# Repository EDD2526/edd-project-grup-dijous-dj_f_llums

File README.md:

View this project on [CADLAB.io](https://cadlab.io/project/30200). 

# Projecte LLUMS

>**Autors:** 
>Martina Camprubí i Clara Rosaura

----------

## Objectiu

>PCB per control·lar les llums d'un vehicle a través d'un microcontrolador i comunicació CAN. 

## Diagrama de blocs

>

### Descripció/funcionalitat de cada bloc

  * ZONA D'ALIMENTACIÓ:
	*V-BAT 12V: Entrada de tensió provinent de la bateria del vehicle.
	*DC-DC LM2596: Converteix els 12V a 5V.
	*LDO LM1117: Redueix els 5V a 3.3V per alimentar la lògica digital.
  * CONTROL PRINCIPAL:
	*MICROCONTROLADOR: Processa entrades i controla sortides del Sistema.
	*BOTONERA: Permet a l'usuari seleccionar les diferents funcions de llum i motor.
	*USART / DEBUG: Interfície per comunicació i depuració del Sistema.
  * ZONA DIGITAL:
	*SENSOR DE LLUM (BH1750): Mesura la llum ambiental via I2C per automatizar funcions.
	*TRANSCEIVER CAN (MCP2551): Adapta els senyals del micro al bus CAN del vehicle.
	*BUS CAN: Xarxa de comuniació amb altres sistemes del vehicle.
  * ZONA DE POTÈNCIA:
	*DRIVERS MOSFET (IRLZ44N): Actuen com interruptors per controlar càrregues de 12V.
	*SISTEMA DE LLUMS: Conjunt de llums del vehicle controlades electrònicament.
	*MOTOR NETEJA-FARS: Actuador de 12V per al sistema de neteja de fars.

-----------

## Requisits / Especificacions

  * Alimentació; 12V, regulada 5V
  * Microcontrolador PIC18xxxxxxxxx
  * ...

-----------

## Components

| Descripci&#243; | Ref | Package |Datasheet | Prove&#239;dor | Preu | Unitats |
| --- | --- | --- | --- | ---| --- | --- |
| Microcontrolador | PIC18F26Q83-I/SS | SOIC-28 |[Datasheet](https://www.mouser.es/datasheet/2/268/PIC18F27_47_57Q83_Preliminary_Data_Sheet_40002265B-2887591.pdf) | [Mouser](https://www.mouser.es/c/?q=PIC18F27Q83-I%2FSO)| 2,17&euro;| 1x |
| XTAL-Ressonador | CSTCR7M99G53-R0 | SMD |[Datasheet](https://www.mouser.es/datasheet/2/281/p16e-522700.pdf) | [Mouser](https://www.mouser.es/ProductDetail/Murata-Electronics/CSTCR7M99G53-R0?qs=Zd9RUO93%2Fo7cnwzsujIkpA%3D%3D)  | 0,27&euro; | 1x |

-----------

## Software

### Eines:

  * KiCad 9.0 o superior
  * 

### Configuraci&#243; :

  * 

### Funcionalitats:

  * 

-----------

## Historial de canvis

| Data | Autor     | Branch | Versi&#243; | Descripci&#243; |
| --- | --- | --- | --- | --- |
|  28/03/2023 | mlopez | Master | initial commit | Primera versi&#243; d'esquem&#224;tic i selecci&#243; de components |

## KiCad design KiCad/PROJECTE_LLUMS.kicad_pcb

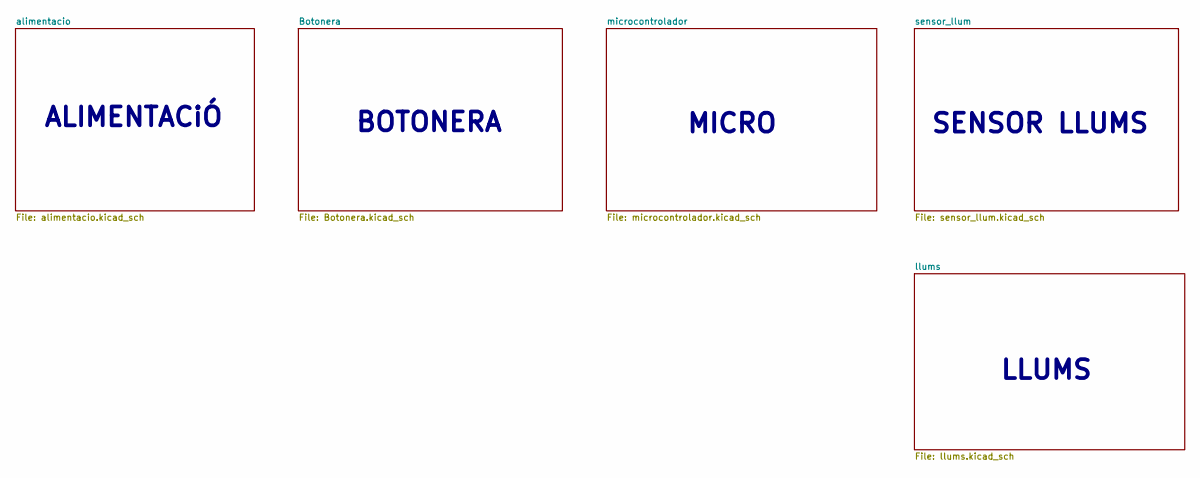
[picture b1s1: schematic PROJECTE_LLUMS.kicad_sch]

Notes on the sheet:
ALIMENTACiÓ
MICRO
LLUMS
BOTONERA
SENSOR LLUMS

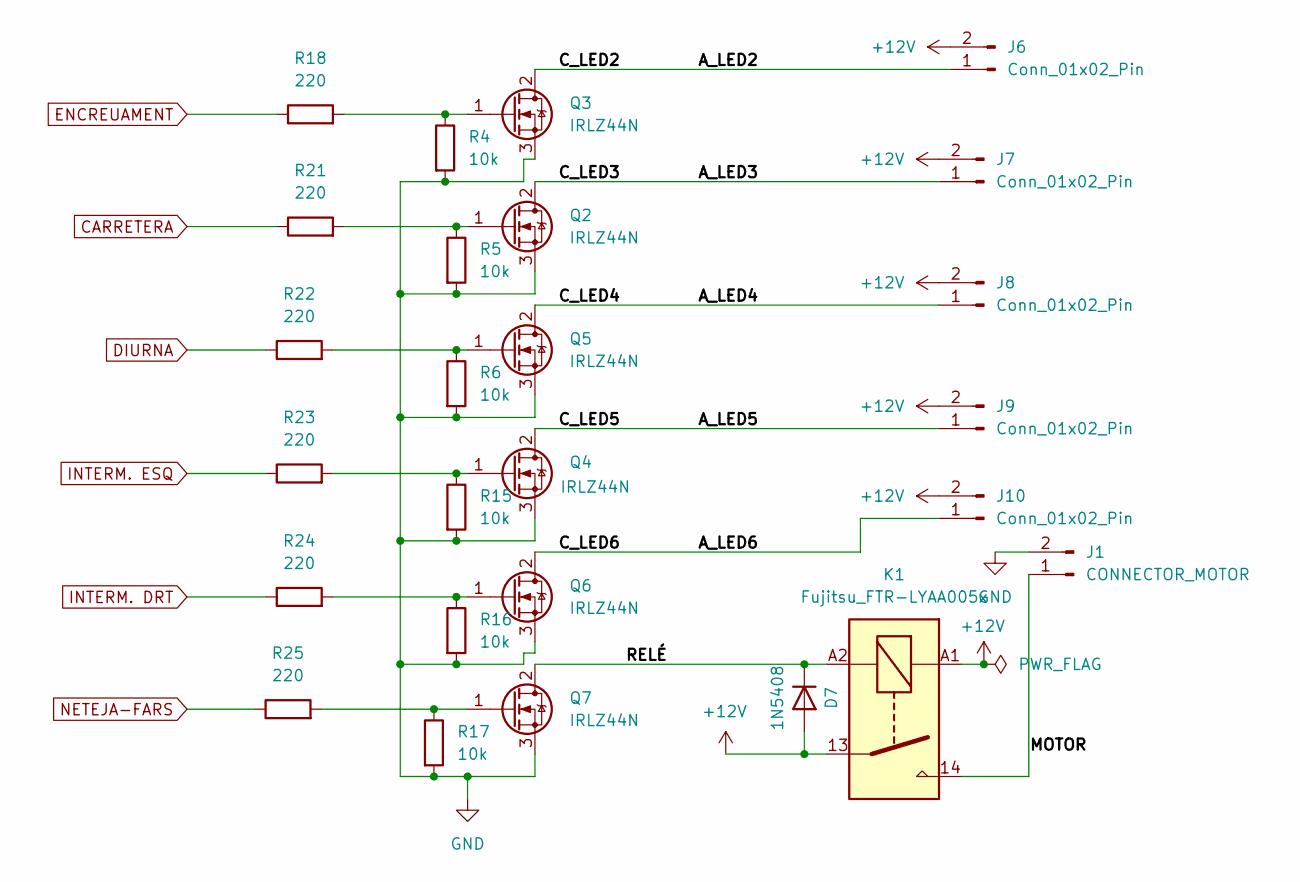
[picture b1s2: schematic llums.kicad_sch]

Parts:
D7: 1N5408; D_DO-201AD_P15.24mm_Horizontal
J1: CONNECTOR_MOTOR; JST_VH_B2P-VH_1x02_P3.96mm_Vertical
J6: Conn_01x02_Pin; TerminalBlock_Phoenix_MKDS-1,5-2-5.08_1x02_P5.08mm_Horizont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
J7, J8, J9, J10: Conn_01x02_Pin; TerminalBlock_MaiXu_MX126-5.0-02P_1x02_P5.00mm
K1: Fujitsu_FTR-LYAA005x; Relay_1-Form-C_Schrack-RYII_RM3.2mm
Q2, Q3, Q4, Q5, Q6, Q7: IRLZ44N; TO-220-3_Vertical
R4, R5, R6, R15, R16, R17: 10k; R_0805_2012Metric_Pad1.20x1.40mm_HandSolder
R18, R21, R22, R23, R24, R25: 220; R_0805_2012Metric_Pad1.20x1.40mm_HandSolder

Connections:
+12V: D7.2 (A), J6.2, J7.2, J8.2, J9.2, J10.2, K1.13, K1.A1
/llums/A_LED2: J6.1, Q3.2 (D)
/llums/A_LED3: J7.1, Q2.2 (D)
/llums/A_LED4: J8.1, Q5.2 (D)
/llums/A_LED5: J9.1, Q4.2 (D)
/llums/A_LED6: J10.1, Q6.2 (D)
/llums/MOTOR: J1.1, K1.14
/llums/RELÉ: D7.1 (K), K1.A2, Q7.2 (D)
CARRETERA: R21.1; also elsewhere on the board
DIURNA: R22.1; also elsewhere on the board
ENCREUAMENT: R18.1; also elsewhere on the board
GND: J1.2, Q2.3 (S), Q3.3 (S), Q4.3 (S), Q5.3 (S), Q6.3 (S), Q7.3 (S), R4.2, R5.2, R6.2, R15.2, R16.2, R17.2; also elsewhere on the board
INTERM. DRT: R24.1; also elsewhere on the board
INTERM. ESQ: R23.1; also elsewhere on the board
NETEJA-FARS: R25.1; also elsewhere on the board
unnamed: Q2.1 (G), R5.1, R21.2
unnamed: Q3.1 (G), R4.1, R18.2
unnamed: Q4.1 (G), R15.1, R23.2
unnamed: Q5.1 (G), R6.1, R22.2
unnamed: Q6.1 (G), R16.1, R24.2
unnamed: Q7.1 (G), R17.1, R25.2

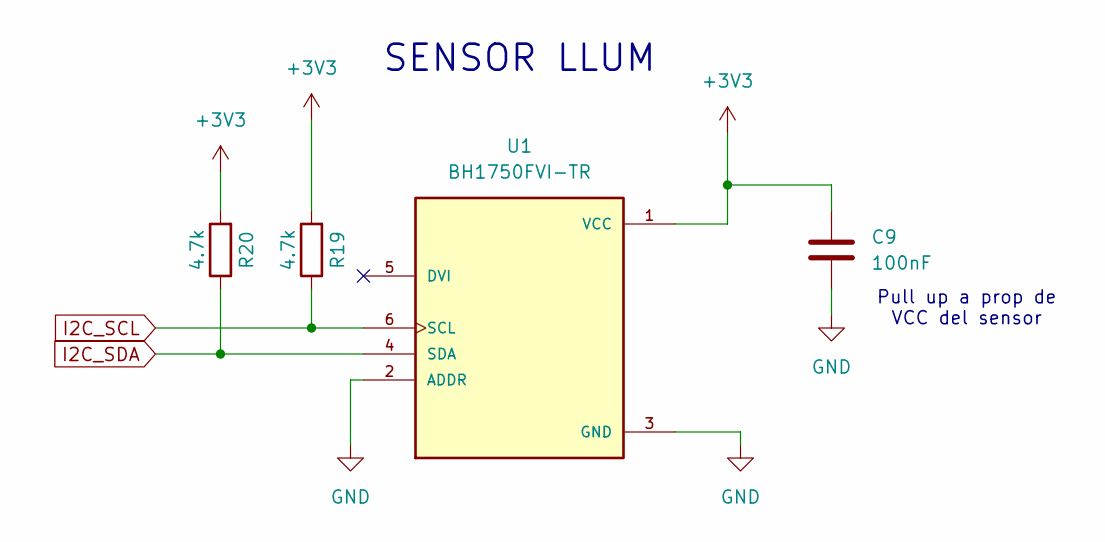
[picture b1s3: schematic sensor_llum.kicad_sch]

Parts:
C9: 100nF; C_0805_2012Metric_Pad1.18x1.45mm_HandSolder
R19, R20: 4.7k; R_0805_2012Metric_Pad1.20x1.40mm_HandSolder
U1: BH1750FVI-TR; XDCR_BH1750FVI-TR; PARTREV D

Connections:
+3V3: C9.1, R19.2, R20.2, U1.1 (VCC); also elsewhere on the board
GND: C9.2, U1.2 (ADDR), U1.3 (GND); also elsewhere on the board
I2C_SCL: R19.1, U1.6 (SCL); also elsewhere on the board
I2C_SDA: R20.1, U1.4 (SDA); also elsewhere on the board

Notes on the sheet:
SENSOR LLUM
Pull up a prop de VCC del sensor

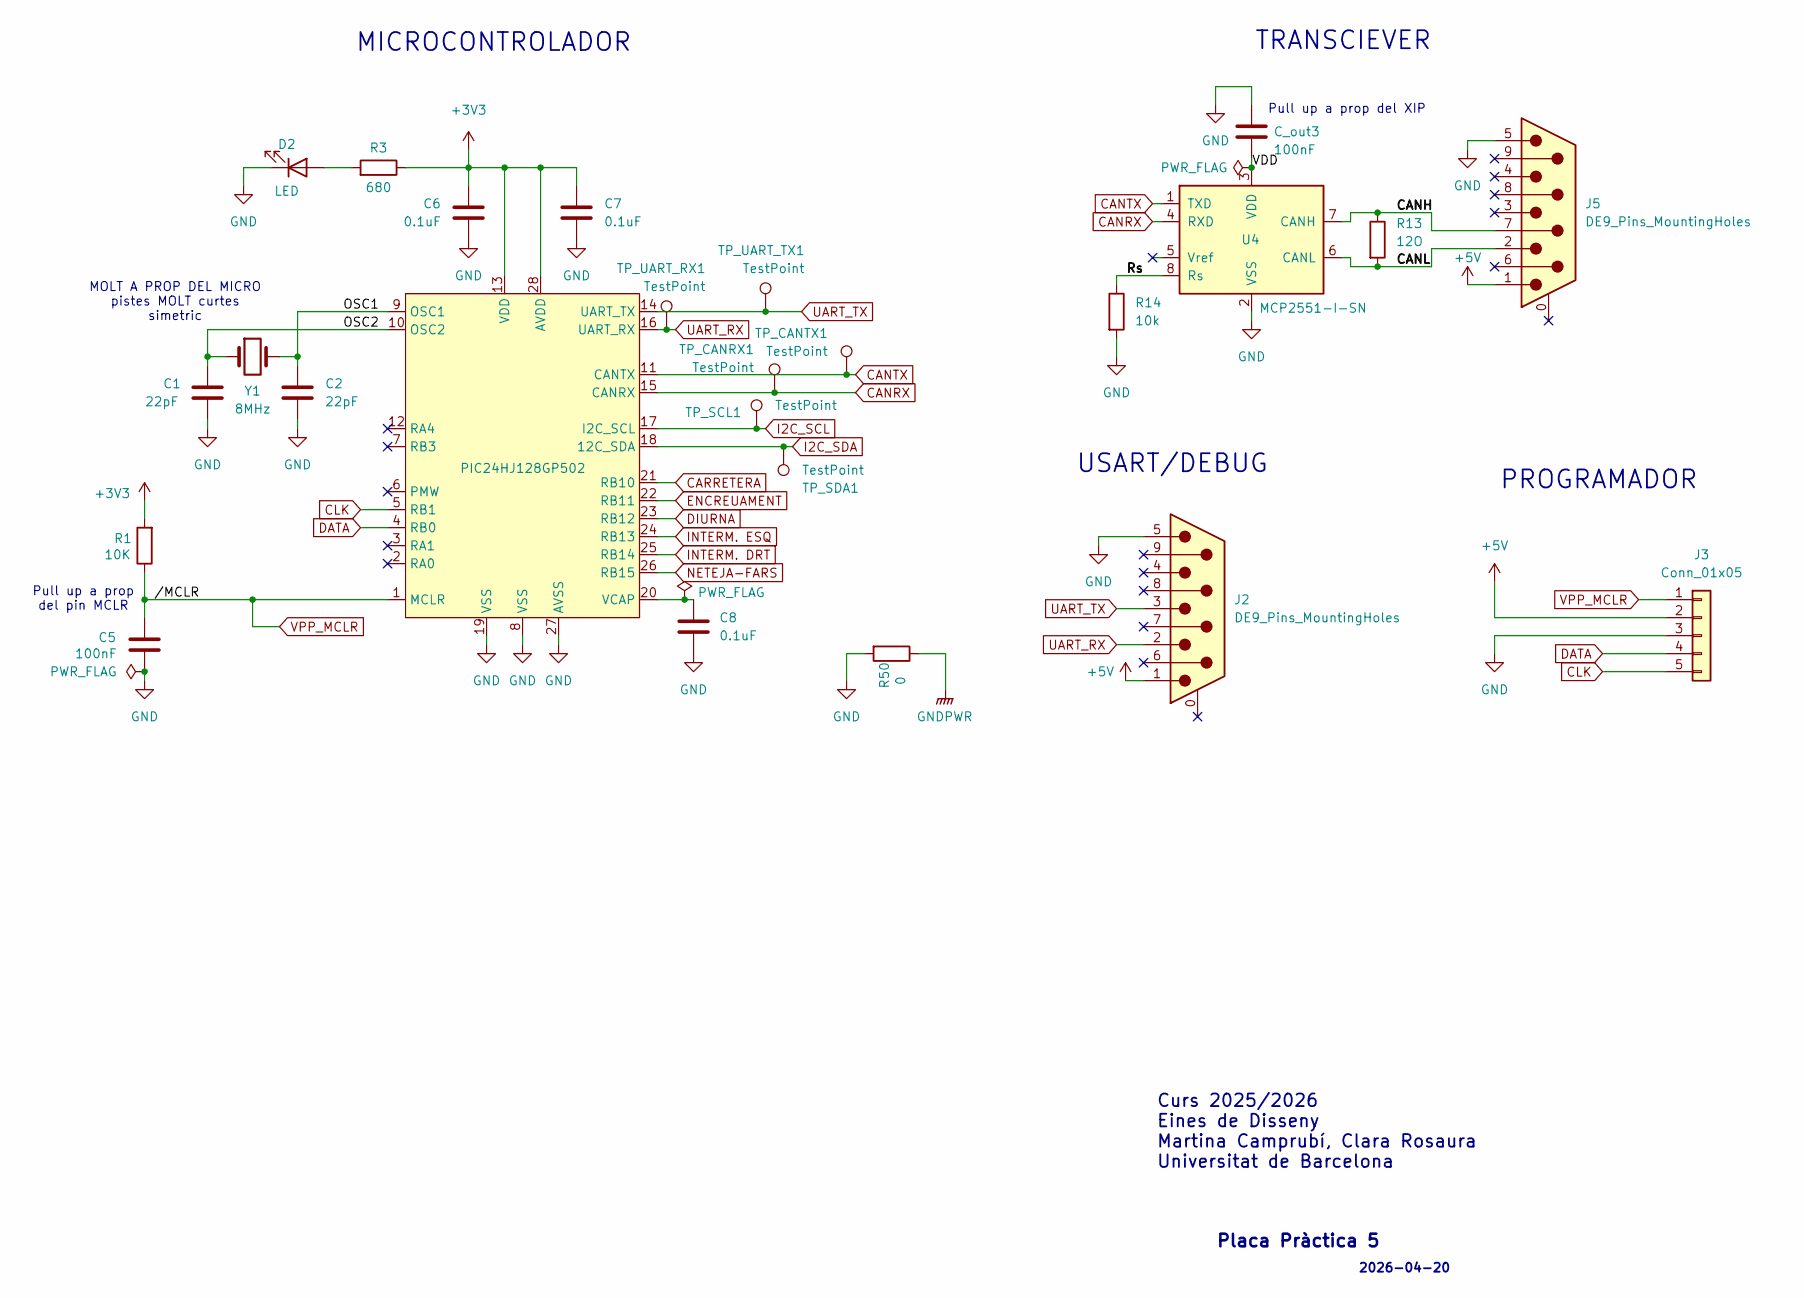
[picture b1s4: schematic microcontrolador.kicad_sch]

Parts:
C1, C2: 22pF; C_0805_2012Metric_Pad1.18x1.45mm_HandSolder
C5: 100nF; C_0805_2012Metric_Pad1.18x1.45mm_HandSolder
C6, C7, C8: 0.1uF; C_0805_2012Metric_Pad1.18x1.45mm_HandSolder
C_out3: 100nF; C_0805_2012Metric_Pad1.18x1.45mm_HandSolder
D2: LED; LED_0805_2012Metric_Pad1.15x1.40mm_HandSolder
J2, J5: DE9_Pins_MountingHoles; DSUB-9_Pins_Horizontal_P2.77x2.84mm_EdgePinOffset4.94mm_Hou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
J3: Conn_01x05; PinHeader_1x05_P2.54mm_Vertical
R1: 10K; R_0805_2012Metric_Pad1.20x1.40mm_HandSolder
R3: 680; R_0805_2012Metric_Pad1.20x1.40mm_HandSolder
R13: 12O; R_0805_2012Metric_Pad1.20x1.40mm_HandSolder
R14: 10k; R_0805_2012Metric_Pad1.20x1.40mm_HandSolder
R50: 0; R_0805_2012Metric_Pad1.20x1.40mm_HandSolder
TP_CANRX1: TestPoint; PinHeader_1x01_P2.54mm_Vertical
TP_CANTX1: TestPoint; PinHeader_1x01_P2.54mm_Vertical
TP_SCL1: TestPoint; PinHeader_1x01_P2.54mm_Vertical
TP_SDA1: TestPoint; PinHeader_1x01_P2.54mm_Vertical
TP_UART_RX1: TestPoint; PinHeader_1x01_P2.54mm_Vertical
TP_UART_TX1: TestPoint; PinHeader_1x01_P2.54mm_Vertical
U2: (no value)
U4: MCP2551-I-SN; SOIC-8_3.9x4.9mm_P1.27mm
U7: PIC24HJ128GP502; SOIC127P1030X265-28N
Y1: 8MHz; Crystal_SMD_3225-4Pin_3.2x2.5mm_HandSoldering

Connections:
+3V3: C6.1, C7.1, R1.2, R3.1, U7.13 (VDD), U7.28 (AVDD); also elsewhere on the board
+5V: J2.1, J3.2, J5.1; also elsewhere on the board
/microcontrolador/CANH: J5.7, R13.1, U4.7 (CANH)
/microcontrolador/CANL: J5.2, R13.2, U4.6 (CANL)
/microcontrolador/OSC1: C2.1, U7.9 (OSC1), Y1.2
/microcontrolador/OSC2: C1.1, U7.10 (OSC2), Y1.1
/microcontrolador/Rs: R14.1, U4.8 (Rs)
/microcontrolador/VDD: C_out3.2, U4.3 (VDD)
CANRX: TP_CANRX1.1, U4.4 (RXD), U7.15 (CANRX)
CANTX: TP_CANTX1.1, U4.1 (TXD), U7.11 (CANTX)
CARRETERA: U7.21 (RB10); also elsewhere on the board
CLK: J3.5, U7.5 (RB1)
DATA: J3.4, U7.4 (RB0)
DIURNA: U7.23 (RB12); also elsewhere on the board
ENCREUAMENT: U7.22 (RB11); also elsewhere on the board
GND: C1.2, C2.2, C5.2, C6.2, C7.2, C8.2, C_out3.1, D2.1 (K), J2.5, J3.3, J5.5, R14.2, R50.2, U4.2 (VSS), U7.8 (VSS), U7.19 (VSS), U7.27 (AVSS); also elsewhere on the board
GNDPWR: R50.1; also elsewhere on the board
I2C_SCL: TP_SCL1.1, U7.17 (I2C_SCL); also elsewhere on the board
I2C_SDA: TP_SDA1.1, U7.18 (12C_SDA); also elsewhere on the board
INTERM. DRT: U7.25 (RB14); also elsewhere on the board
INTERM. ESQ: U7.24 (RB13); also elsewhere on the board
NETEJA-FARS: U7.26 (RB15); also elsewhere on the board
unnamed: D2.2 (A), R3.2
unnamed: C8.1, U7.20 (VCAP)
UART_RX: J2.2, TP_UART_RX1.1, U7.16 (UART_RX)
UART_TX: J2.3, TP_UART_TX1.1, U7.14 (UART_TX)
VPP_MCLR: C5.1, J3.1, R1.1, U7.1 (MCLR)

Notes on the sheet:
TRANSCIEVER
USART/DEBUG
PROGRAMADOR
2026-04-20
MOLT A PROP DEL MICRO pistes MOLT curtes simetric
Curs 2025/2026 Eines de Disseny Martina Camprubí, Clara Rosaura Universitat de Barcelona
MICROCONTROLADOR
Pull up a prop del pin MCLR
Pull up a prop del XIP
Placa Pràctica 5

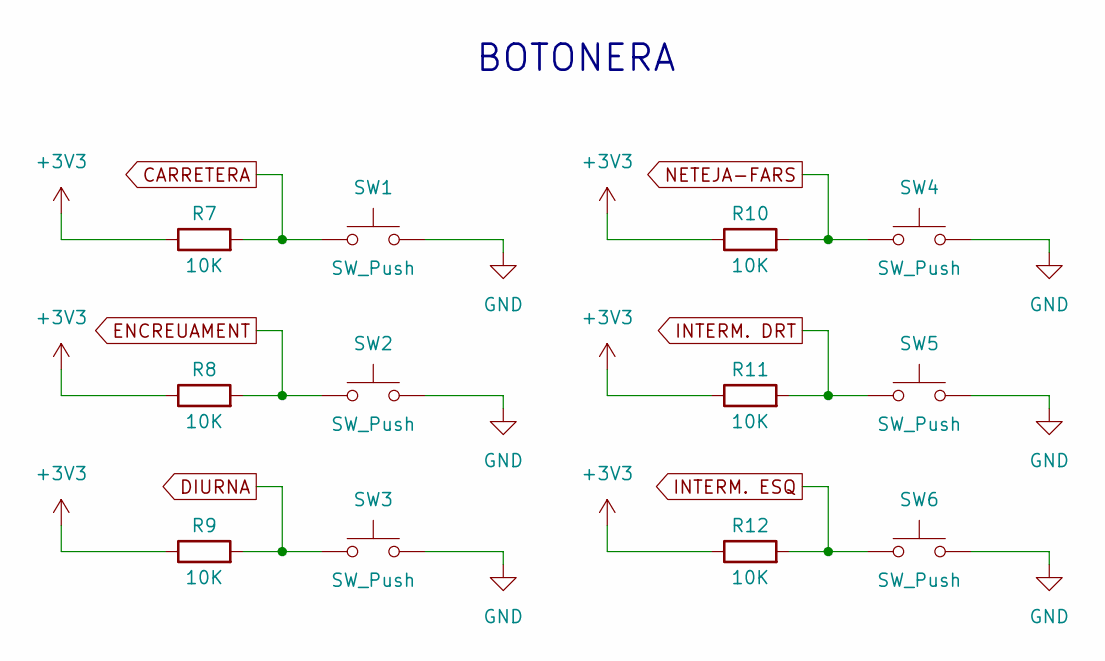
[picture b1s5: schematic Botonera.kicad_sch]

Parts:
R7, R8, R9, R10, R11, R12: 10K; R_0805_2012Metric_Pad1.20x1.40mm_HandSolder
SW1, SW2, SW3, SW4, SW5, SW6: SW_Push; SW_PUSH_6mm

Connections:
+3V3: R7.1, R8.1, R9.1, R10.1, R11.1, R12.1; also elsewhere on the board
CARRETERA: R7.2, SW1.1; also elsewhere on the board
DIURNA: R9.2, SW3.1; also elsewhere on the board
ENCREUAMENT: R8.2, SW2.1; also elsewhere on the board
INTERM. DRT: R11.2, SW5.1; also elsewhere on the board
INTERM. ESQ: R12.2, SW6.1; also elsewhere on the board
NETEJA-FARS: R10.2, SW4.1; also elsewhere on the board
unnamed: SW1.2, SW2.2, SW3.2, SW4.2, SW5.2, SW6.2

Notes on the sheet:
BOTONERA

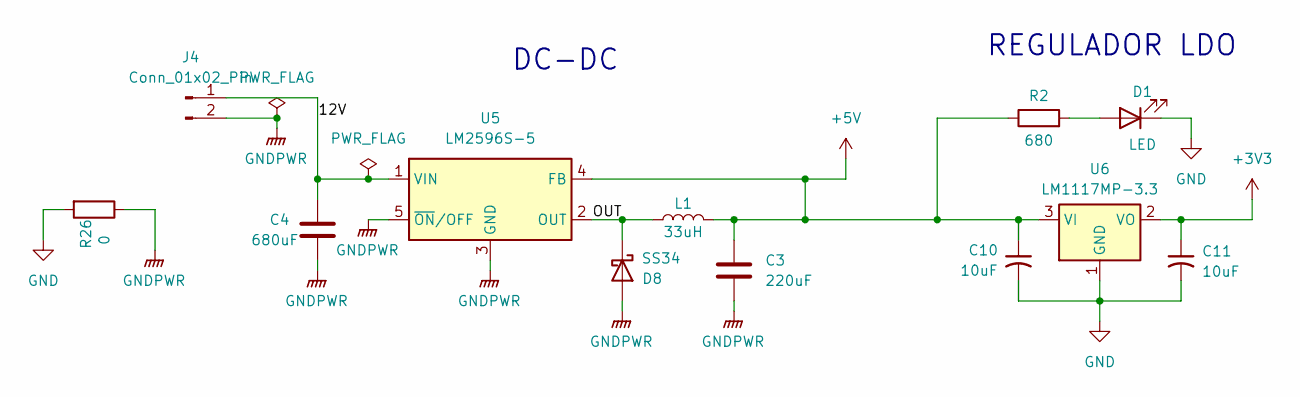
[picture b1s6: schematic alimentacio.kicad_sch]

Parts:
C3: 220uF; CP_Elec_6.3x5.4
C4: 680uF; C_0805_2012Metric_Pad1.18x1.45mm_HandSolder
C10, C11: 10uF; C_0805_2012Metric_Pad1.18x1.45mm_HandSolder
D1: LED; LED_0805_2012Metric_Pad1.15x1.40mm_HandSolder
D8: SS34; D_SMA
J4: Conn_01x02_Pin; TerminalBlock_MaiXu_MX126-5.0-02P_1x02_P5.00mm
L1: 33uH; L_7.3x7.3_H4.5
R2: 680; R_0805_2012Metric_Pad1.20x1.40mm_HandSolder
R26: 0; R_0805_2012Metric_Pad1.20x1.40mm_HandSolder
U5: LM2596S-5; TO-263-5_TabPin3
U6: LM1117MP-3.3; SOT-223-3_TabPin2

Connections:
+3V3: C11.1, U6.2 (VO); also elsewhere on the board
+5V: C3.1, C10.1, L1.2, R2.1, U5.4 (FB), U6.3 (VI); also elsewhere on the board
/alimentacio/12V: C4.1, J4.1, U5.1 (VIN)
/alimentacio/OUT: D8.1 (K), L1.1, U5.2 (OUT)
GND: C10.2, C11.2, D1.1 (K), R26.2, U6.1 (GND); also elsewhere on the board
GNDPWR: C3.2, C4.2, D8.2 (A), J4.2, R26.1, U5.3 (GND), U5.5 (~ON/OFF); also elsewhere on the board
unnamed: D1.2 (A), R2.2

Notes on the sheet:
DC-DC
REGULADOR LDO

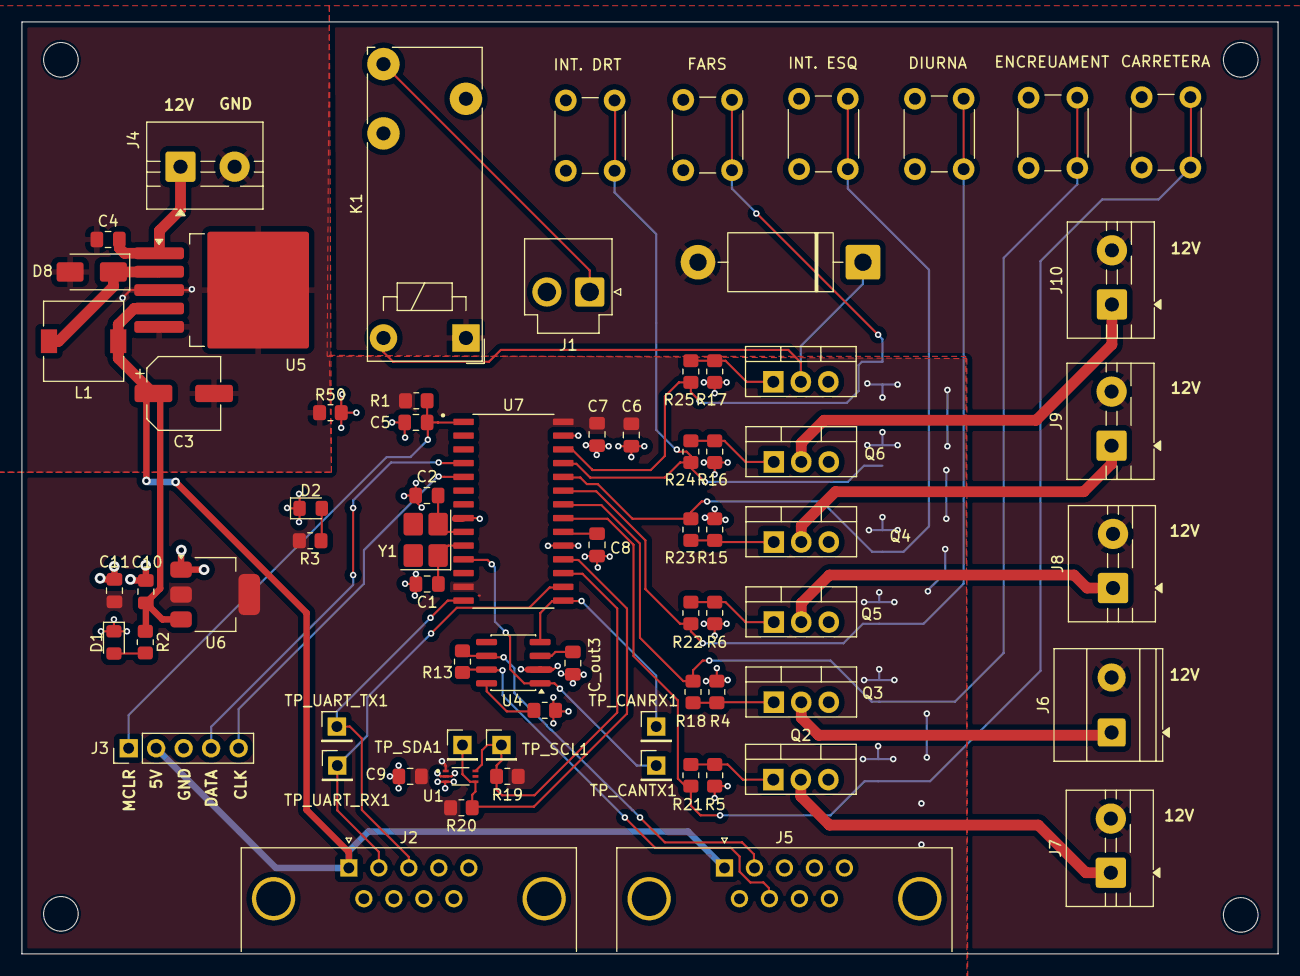
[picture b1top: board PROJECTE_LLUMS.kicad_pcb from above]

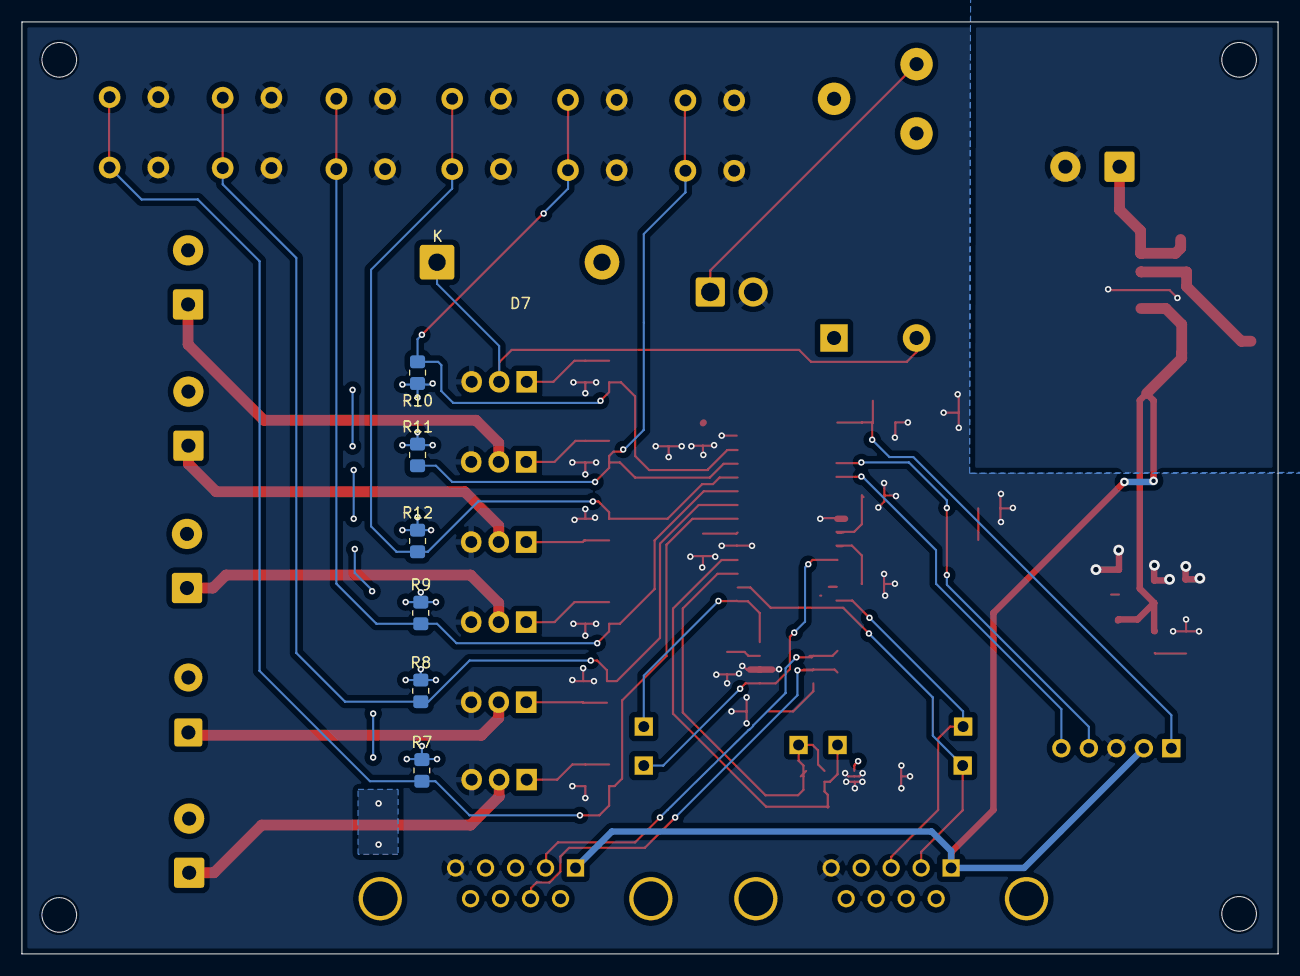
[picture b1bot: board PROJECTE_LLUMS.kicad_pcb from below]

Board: 2 copper layers, 116.1 x 86.1 mm, 78 parts (6 on the bottom side), 44 nets.

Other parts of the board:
CARRETERA: SW_Push; SW_PUSH_6mm
DIURNA: SW_Push; SW_PUSH_6mm
ENCREUAMENT: SW_Push; SW_PUSH_6mm
FARS: SW_Push; SW_PUSH_6mm
INT. DRT, INT. ESQ: SW_Push; SW_PUSH_6mm

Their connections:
CARRETERA: CARRETERA.1; also elsewhere on the board
DIURNA: DIURNA.1; also elsewhere on the board
ENCREUAMENT: ENCREUAMENT.1; also elsewhere on the board
GND: CARRETERA.2, DIURNA.2, ENCREUAMENT.2, FARS.2, INT. DRT.2, INT. ESQ.2; also elsewhere on the board
INTERM. DRT: INT. DRT.1; also elsewhere on the board
INTERM. ESQ: INT. ESQ.1; also elsewhere on the board
NETEJA-FARS: FARS.1; also elsewhere on the board

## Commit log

2026-03-12 canvi de nom
2026-03-12 kitkat creat
2026-03-16 Backlink to CADLAB.io has been added.
2026-03-17 DC-DC i transciever
2026-03-17 part llums
2026-03-19 llums bé pagina nova
2026-03-19 llums bé amb les etiquetes bé
2026-03-19 esquemàtic amb totes les cel·les
2026-03-21 he afegit tot lo del old al new
2026-03-21 he canviat el micro
2026-03-24 ERC i footprints
2026-03-24 placement (falten LEDs)
2026-03-24 routing
2026-03-25 correcció d'errors CADLAB, falten els de llums i un parell que no entenc
2026-03-25 Esquemàtic acabat amb llums incorporades
2026-03-26 errors cadlab
2026-03-26 errors pcb
2026-03-26 relé fet
2026-03-26 remove auto saved files
2026-03-28 alguns errors de CADLAB i he canivat d'ordre els LEDs i els drivers a la PCB.
2026-03-28 prova README
2026-03-28 update README 2
2026-03-28 update README (¿)
2026-04-01 modificacions cadlab
2026-04-07 he esborrat els esquemàtics del transciever i USART
2026-04-09 Relé??
2026-04-09 presentar
2026-04-09 correccions Manel
2026-04-13 algo de routing
2026-04-15 Connectors amb huellas
2026-04-16 coses
2026-04-16 presentació
2026-04-16 routing def
2026-04-17 test points schematic
2026-04-20 test points ALIMENTACIO, UART, CAN
2026-04-20 errors de connexio no solucionats
2026-04-21 CADLAB
2026-04-27 errors 3V3
2026-04-29 LLums finals amb resistències afegides
2026-04-29 errors finals
2026-04-30 push final (?)
2026-04-30 PRESENTACIÓ FINAL
